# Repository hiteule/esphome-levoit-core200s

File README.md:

# ESPHome Levoit Core200s

An electronic board designed to replace the Levoit Core 200s air purifier control board (because I broke it).
Only the "Fan speed" and "Power" buttons are functional.
The air purifier is exposed via [ESPHome], which enables integration with [HomeAssistant].

## PCB

The board must be connected to the "power board" of the air purifier via the JST connector on J1.
This connector supplies 5V on pin 1. Take care to connect it the right way.

The ESP32 should be flashed with ESPHome via J2(TX), J3(RX), J6(RTS), J7(DTR) J8(3.3V), J9(GND).
For this, you can use my [ESP/Atmega programmer].

The card was designed with [Kicad]. The sources (schematic & board) are in the "pcb" folder.

## Software

The ESP32 is exposing the Air Purifier in Home Assisant. To do it, we use [ESPHome].
To do so:
* Install the ESPHome module on [HomeAssistant].
* Plug the board to your computer with J2(TX), J3(RX), J6(RTS), J7(DTR) J8(3.3V), J9(GND) and the [ESP/Atmega programmer].
* In the ESPHome module, create a new device.
* Update your ESPHome device with the `levoit-core200s.yaml` file.
* Install it on the ESP.

Now you can unplug the ESP from your computer, install it into the air purifier and connect it via J1.
ESP should boot normally and the air purifier should be visible in [HomeAssistant].

[HomeAssistant]: https://www.home-assistant.io
[ESPHome]: https://esphome.io/
[ESP/Atmega programmer]: https://github.com/hiteule/programmer-esp-atmega
[Kicad]: https://www.kicad.org

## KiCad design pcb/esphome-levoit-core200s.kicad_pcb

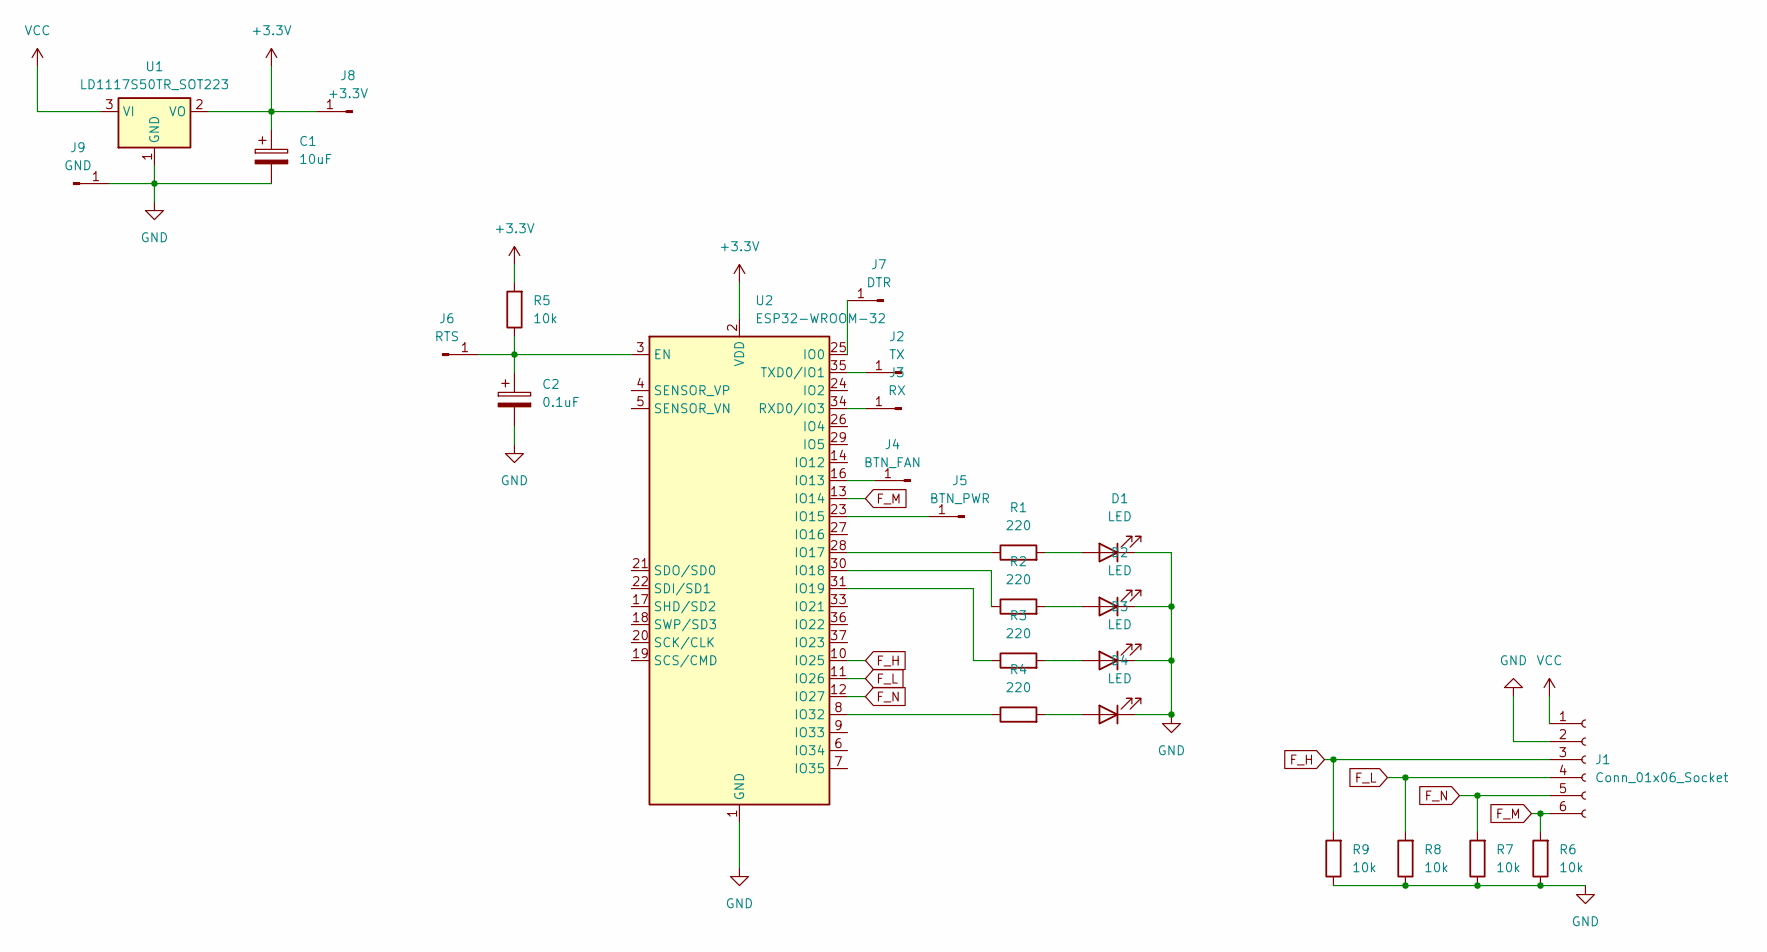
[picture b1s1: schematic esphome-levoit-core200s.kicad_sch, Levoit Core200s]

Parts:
C1: 10uF; CP_Radial_D5.0mm_P2.50mm
C2: 0.1uF; CP_Radial_D5.0mm_P2.50mm
D1, D2, D3, D4: LED; LED_D3.0mm
J1: Conn_01x06_Socket; JST_PH_S6B-PH-K_1x06_P2.00mm_Horizontal
J2: TX; PinHeader_1x01_P1.00mm_Vertical
J3: RX; PinHeader_1x01_P1.00mm_Vertical
J4: BTN_FAN; PinHeader_1x01_P1.00mm_Vertical
J5: BTN_PWR; PinHeader_1x01_P1.00mm_Vertical
J6: RTS; PinHeader_1x01_P1.00mm_Vertical
J7: DTR; PinHeader_1x01_P1.00mm_Vertical
J8: +3.3V; PinHeader_1x01_P1.00mm_Vertical
J9: GND; PinHeader_1x01_P1.00mm_Vertical
R1, R2, R3, R4: 220; R_Axial_DIN0204_L3.6mm_D1.6mm_P5.08mm_Horizontal
R5, R6, R7, R8, R9: 10k; R_Axial_DIN0204_L3.6mm_D1.6mm_P5.08mm_Horizontal
U1: LD1117S50TR_SOT223; SOT-223-3_TabPin2
U2: ESP32-WROOM-32

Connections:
+3.3V: C1.1, J8.1, R5.2, U1.2 (VO), U2.2 (VDD)
F_H: J1.3, R9.2, U2.10 (IO25)
F_L: J1.4, R8.2, U2.11 (IO26)
F_M: J1.6, R6.2, U2.13 (IO14)
F_N: J1.5, R7.2, U2.12 (IO27)
GND: C1.2, C2.2, D1.1 (K), D2.1 (K), D3.1 (K), D4.1 (K), J1.2, J9.1, R6.1, R7.1, R8.1, R9.1, U1.1 (GND), U2.1 (GND), U2.15 (GND), U2.38 (GND), U2.39 (GND)
unnamed: D1.2 (A), R1.2
unnamed: D2.2 (A), R2.2
unnamed: D3.2 (A), R3.2
unnamed: D4.2 (A), R4.2
unnamed: J2.1, U2.35 (TXD0/IO1)
unnamed: J3.1, U2.34 (RXD0/IO3)
unnamed: J4.1, U2.16 (IO13)
unnamed: J5.1, U2.23 (IO15)
unnamed: C2.1, J6.1, R5.1, U2.3 (EN)
unnamed: J7.1, U2.25 (IO0)
unnamed: R1.1, U2.28 (IO17)
unnamed: R2.1, U2.30 (IO18)
unnamed: R3.1, U2.31 (IO19)
unnamed: R4.1, U2.8 (IO32)
VCC: J1.1, U1.3 (VI)

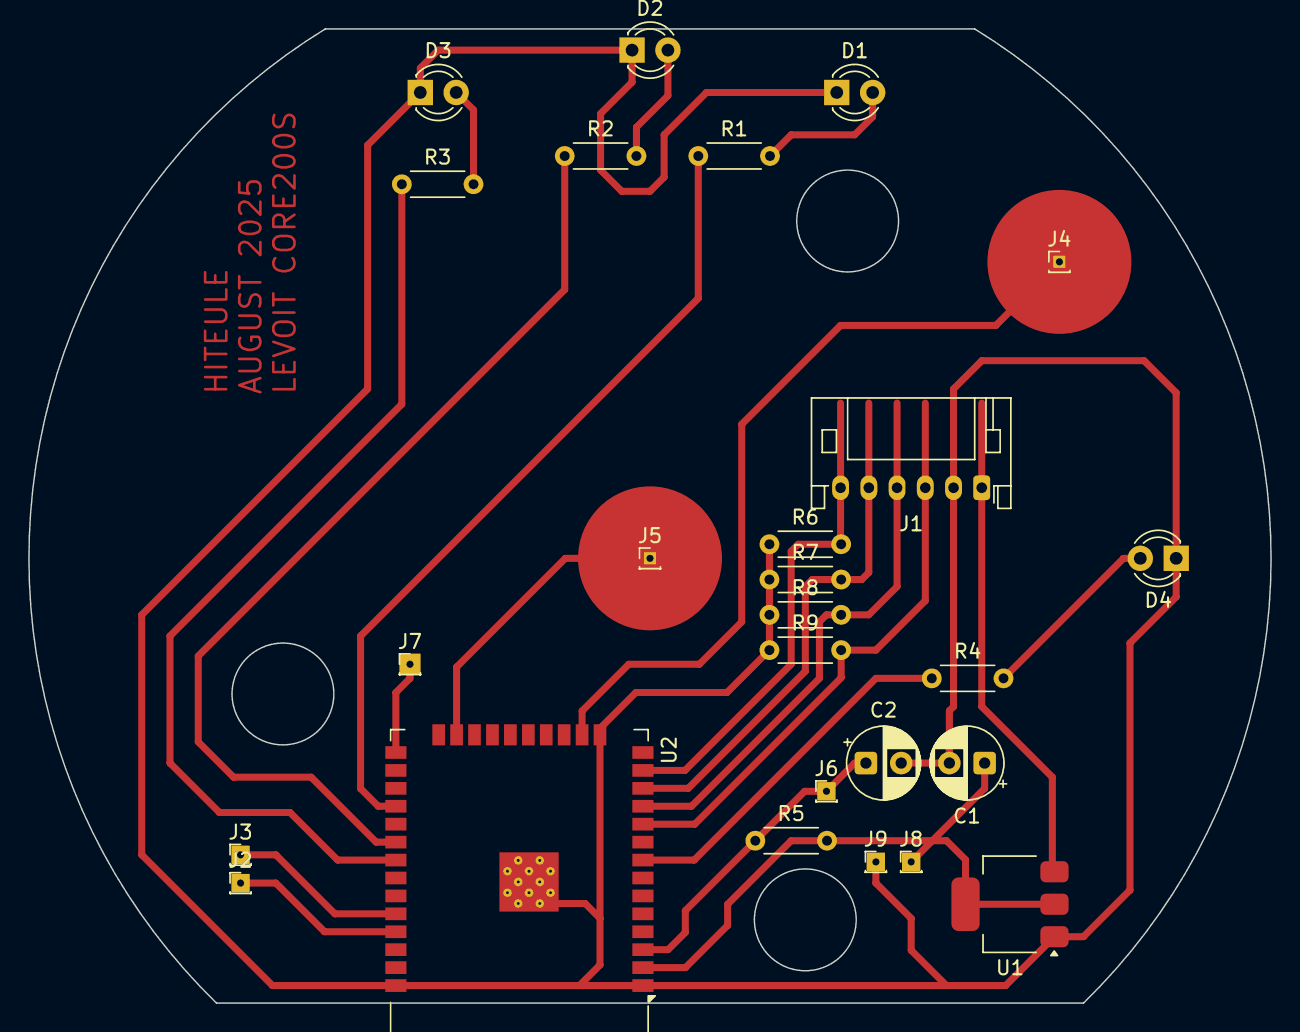
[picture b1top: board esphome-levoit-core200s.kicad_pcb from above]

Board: 2 copper layers, 88.0 x 69.0 mm, 26 parts (0 on the bottom side), 21 nets.

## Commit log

2025-08-14 Fix readme
2025-08-14 Add gitignore
2025-08-14 Add img
2025-09-05 fix levoit-core200s.yaml
